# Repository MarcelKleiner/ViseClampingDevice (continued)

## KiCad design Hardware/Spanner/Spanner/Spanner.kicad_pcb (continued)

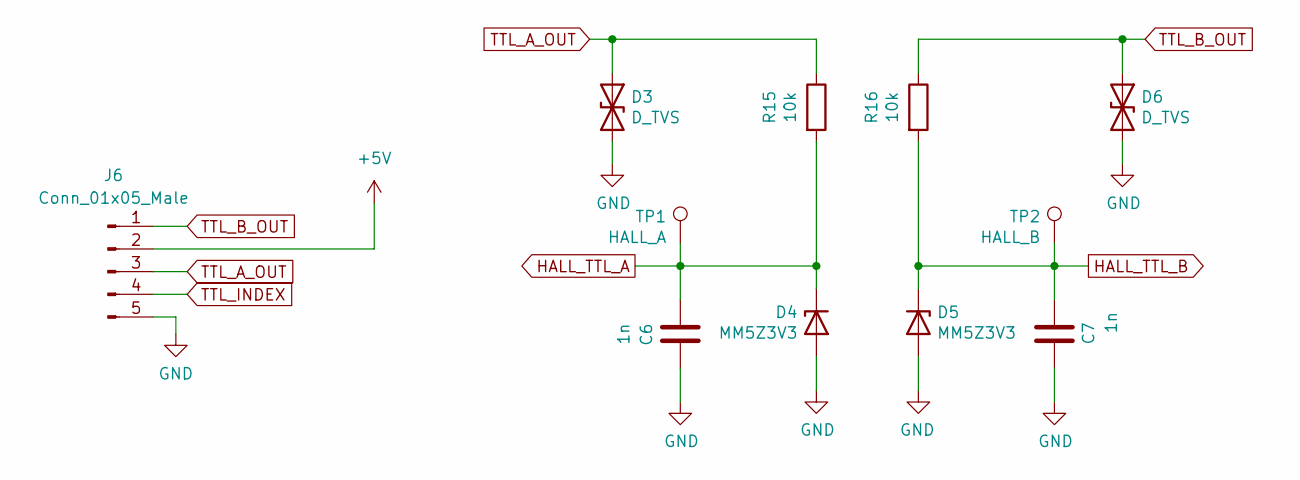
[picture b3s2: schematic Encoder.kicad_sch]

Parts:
C6, C7: 1n; C_0603_1608Metric; Mouser Nr. 581-06035C102K
D3, D6: D_TVS; D_0603_1608Metric; Mouser Nr. 652-CGA0603MLC-24E
D4, D5: MM5Z3V3; D_SOD-523; Mouser Nr. 863-MM5Z3V3T1G
J6: Conn_01x05_Male; PinHeader_1x05_P2.54mm_Vertical
R15, R16: 10k; R_0603_1608Metric; Mouser Nr. 603-RT0603FRE0710KL
TP1: HALL_A; TestPoint_Pad_D1.0mm
TP2: HALL_B; TestPoint_Pad_D1.0mm

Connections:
+5V: J6.2; also elsewhere on the board
GND: C6.1, C7.2, D3.2 (A2), D4.2 (A), D5.2 (A), D6.2 (A2), J6.5; also elsewhere on the board
HALL_TTL_A: C6.2, D4.1 (K), R15.2, TP1.1; also elsewhere on the board
HALL_TTL_B: C7.1, D5.1 (K), R16.2, TP2.1; also elsewhere on the board
TTL_A_OUT: D3.1 (A1), J6.3, R15.1
TTL_B_OUT: D6.1 (A1), J6.1, R16.1
TTL_INDEX: J6.4

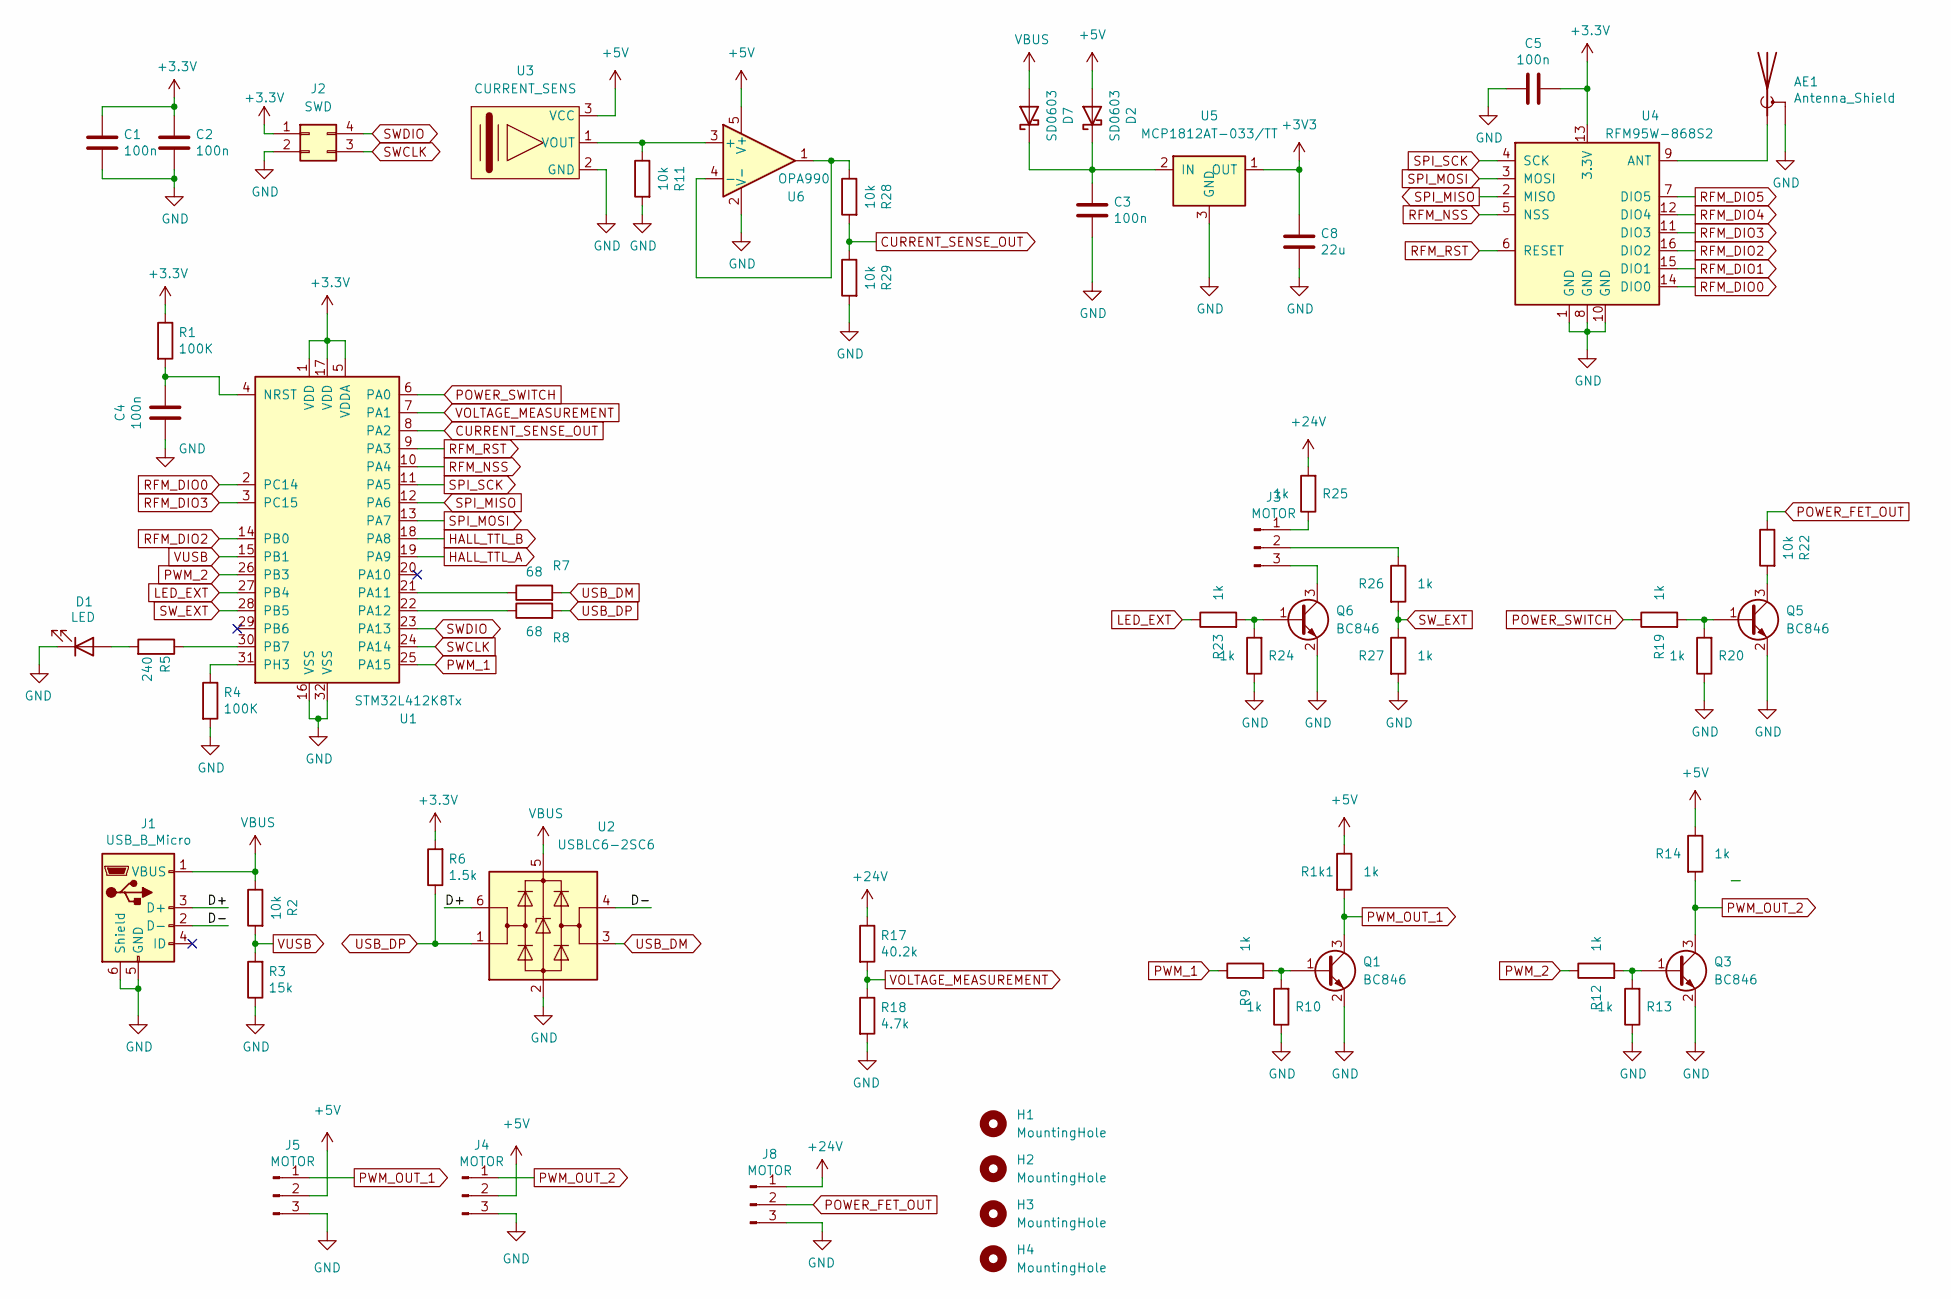
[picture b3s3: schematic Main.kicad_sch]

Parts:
AE1: Antenna_Shield; U.FL_Hirose_U.FL-R-SMT-1_Vertical; Mouser Nr. 712-CONUFL001-SMD-T
C1, C2, C3, C4, C5: 100n; C_0603_1608Metric; Mouser Nr. 187-CL10B104KB8NNWC
C8: 22u; C_0603_1608Metric; Mouser Nr. 187-CL21A226MAYNNNE
D1: LED; LED_0603_1608Metric; Mouser Nr. 710-150060VS75000
D2, D7: SD0603; D_0603_1608Metric; Mouser Nr. 581-SD0603S040S0R2
H1, H2, H3, H4: MountingHole; MountingHole_3.2mm_M3
J1: USB_B_Micro; USB_Micro-B_Wuerth_614105150721_Vertical; Mouser Nr. 710-614105150721
J2: SWD; PinHeader_2x02_P2.54mm_Vertical
J3, J4, J5, J8: MOTOR; PinHeader_1x03_P2.54mm_Vertical
Q1, Q3, Q5, Q6: BC846; SOT-23; Mouser Nr. 771-BC846A235
R1, R4: 100K; R_0603_1608Metric; Mouser Nr. 71-CRCW0603100KFKEAC
R1k1, R9, R10, R12, R13, R14, R19, R20, R23, R24, R25, R26, R27: 1k; R_0603_1608Metric; Mouser Nr. 603-RT0603FRE071KL
R2, R11, R22, R28, R29: 10k; R_0603_1608Metric; Mouser Nr. 603-RT0603FRE0710KL
R3: 15k; R_0603_1608Metric; Mouser Nr. 603-RT0603BRB0715KL
R5: 240; R_0603_1608Metric; Mouser Nr. 603-RC0603FR-13240RL
R6: 1.5k; R_0603_1608Metric; Mouser Nr. 603-RT0603FRE101K5L
R7, R8: 68; R_0603_1608Metric; Mouser Nr. 71-CRCW0603-68-E3
R17: 40.2k; R_0603_1608Metric; Mouser Nr. 754-RR0816P-4022D59C
R18: 4.7k; R_0603_1608Metric; Mouser Nr. 603-RT0603FRE074K7L
U1: STM32L412K8Tx; LQFP-32_7x7mm_P0.8mm; Mouser Nr. 511-STM32L412K8T6
U2: USBLC6-2SC6; SOT-23-6; Mouser Nr. 511-USBLC6-2SC6
U3: CURRENT_SENS; L01Z; Mouser Nr. 838-L01Z050S05
U4: RFM95W-868S2; HOPERF_RFM9XW_SMD; Mouser Nr. 223-RFM95W-868S2
U5: MCP1812AT-033/TT; SOT-23; Mouser Nr. 579-MCP1812AT-033/TT
U6: OPA990; SOT-23-5; Mouser Nr. 595-OPA990IDBVR

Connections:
+5V: D2.2 (A), J4.2, J5.2, R1k1.1, R14.1, U3.3 (VCC), U6.5 (V+); also elsewhere on the board
+24V: J8.1, R17.1, R25.2
/Main/D+: J1.3 (D+), U2.6 (I/O1)
/Main/D-: J1.2 (D-), U2.4 (I/O2)
CURRENT_SENSE_OUT: R28.2, R29.1, U1.8 (PA2)
GND: AE1.2 (Shield), C1.2, C2.2, C3.2, C4.1, C5.1, C8.1, D1.1 (K), J1.5 (GND), J1.6 (Shield), J2.2, J4.3, J5.3, J8.3, Q1.2 (E), Q3.2 (E), Q5.2 (E), Q6.2 (E), R3.1, R4.2, R10.1, R11.2, R13.1, R18.2, R20.1, R24.1, R27.2, R29.2, U1.16 (VSS), U1.32 (VSS), U2.2 (GND), U3.2 (GND), U4.1 (GND), U4.8 (GND), U4.10 (GND), U5.3 (GND), U6.2 (V-); also elsewhere on the board
HALL_TTL_A: U1.19 (PA9); also elsewhere on the board
HALL_TTL_B: U1.18 (PA8); also elsewhere on the board
LED_EXT: R23.1, U1.27 (PB4)
unnamed: AE1.1 (A), U4.9 (ANT)
unnamed: C3.1, D2.1 (K), D7.1 (K), U5.2 (IN)
unnamed: C4.2, R1.2, U1.4 (NRST)
unnamed: D1.2 (A), R5.2
unnamed: J3.1, R25.1
unnamed: J3.2, R26.1
unnamed: J3.3, Q6.3 (C)
unnamed: Q1.1 (B), R9.2, R10.2
unnamed: Q3.1 (B), R12.2, R13.2
unnamed: Q5.1 (B), R19.2, R20.2
unnamed: Q5.3 (C), R22.2
unnamed: Q6.1 (B), R23.2, R24.2
unnamed: R4.1, U1.31 (PH3)
unnamed: R5.1, U1.30 (PB7)
unnamed: R7.1, U1.21 (PA11)
unnamed: R8.1, U1.22 (PA12)
unnamed: R11.1, U3.1 (VOUT), U6.3 (+)
unnamed: R28.1, U6.1, U6.4 (-)
POWER_FET_OUT: J8.2, R22.1
POWER_SWITCH: R19.1, U1.6 (PA0)
PWM_1: R9.1, U1.25 (PA15)
PWM_2: R12.1, U1.26 (PB3)
PWM_OUT_1: J5.1, Q1.3 (C), R1k1.2
PWM_OUT_2: J4.1, Q3.3 (C), R14.2
RFM_DIO0: U1.2 (PC14), U4.14 (DIO0)
RFM_DIO1: U4.15 (DIO1)
RFM_DIO2: U1.14 (PB0), U4.16 (DIO2)
RFM_DIO3: U1.3 (PC15), U4.11 (DIO3)
RFM_DIO4: U4.12 (DIO4)
RFM_DIO5: U4.7 (DIO5)
RFM_NSS: U1.10 (PA4), U4.5 (NSS)
RFM_RST: U1.9 (PA3), U4.6 (RESET)
SPI_MISO: U1.12 (PA6), U4.2 (MISO)
SPI_MOSI: U1.13 (PA7), U4.3 (MOSI)
SPI_SCK: U1.11 (PA5), U4.4 (SCK)
SWCLK: J2.3, U1.24 (PA14)
SWDIO: J2.4, U1.23 (PA13)
SW_EXT: R26.2, R27.1, U1.28 (PB5)
USB_DM: R7.2, U2.3 (I/O2)
USB_DP: R6.1, R8.2, U2.1 (I/O1)
VBUS: D7.2 (A), J1.1 (VBUS), R2.1, U2.5 (VBUS)
VOLTAGE_MEASUREMENT: R17.2, R18.1, U1.7 (PA1)
VUSB: R2.2, R3.2, U1.15 (PB1)

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
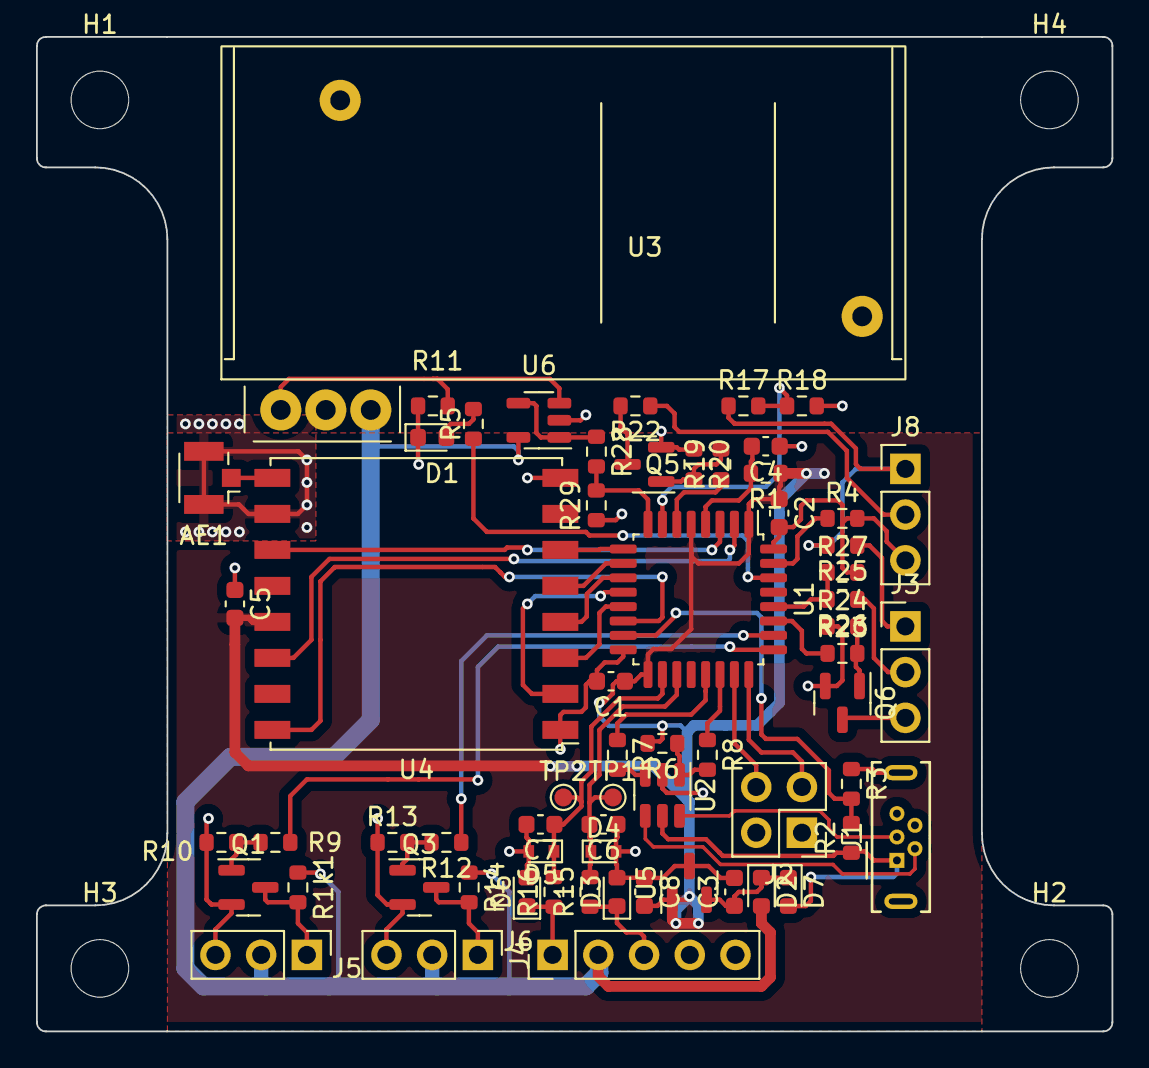
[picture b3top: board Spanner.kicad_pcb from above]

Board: 2 copper layers, 59.8 x 55.2 mm, 68 parts (0 on the bottom side), 52 nets.

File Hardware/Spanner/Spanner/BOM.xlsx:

Item | Qty | Reference(s) | Value | Hersteller Nr. | Mouser Nr.
1 | 1 | AE1 | Antenna_Shield | CONUFL001-SMD-T | 712-CONUFL001-SMD-T
2 | 5 | C1, C2, C3, C4, C5 | 100n | CL10B104KB8NNWC | 187-CL10B104KB8NNWC
3 | 2 | C6, C7 | 1n | 06035C102KAT2A | 581-06035C102K
4 | 1 | C8 | 22u | CL21A226MAYNNNE | 187-CL21A226MAYNNNE
5 | 1 | D1 | LED | 150060VS75000 | 710-150060VS75000
6 | 1 | D2 | SD0603 | SD0603S040S0R2 | 581-SD0603S040S0R2
7 | 2 | D3, D6 | D_TVS | CGA0603MLC-24E | 652-CGA0603MLC-24E
8 | 2 | D4, D5 | MM5Z3V3 | MM5Z3V3T1G | 863-MM5Z3V3T1G
10 | 1 | J1 | USB_B_Micro | 614105150721 | 710-614105150721
15 | 4 | Q1, Q3, Q5, Q6 | BC846 | BC846A,235 | 771-BC846A235
16 | 2 | R1, R4 | 100K | CRCW0603100KFKEAC | 71-CRCW0603100KFKEAC
17 | 13 | R1k1, R9, R10, R12, R13, R14, R19, R20, R23, R24, R25, R26, R27 | 1k | RT0603FRE071KL | 603-RT0603FRE071KL
18 | 8 | R2, R11, R15, R16, R21, R22, R28, R29 | 10k | RT0603FRE0710KL | 603-RT0603FRE0710KL
19 | 1 | R3 | 15k | RT0603BRB0715KL | 603-RT0603BRB0715KL
20 | 1 | R5 | 240 | RC0603FR-13240RL | 603-RC0603FR-13240RL
21 | 1 | R6 | 1.5k | RT0603FRE101K5L | 603-RT0603FRE101K5L
22 | 2 | R7, R8 | 68 | CRCW060368R0FKEA | 71-CRCW0603-68-E3
23 | 1 | R17 | 40.2k | RR0816P-4022-D-59C | 754-RR0816P-4022D59C
24 | 1 | R18 | 4.7k | RT0603FRE074K7 | 603-RT0603FRE074K7L
27 | 1 | U1 | STM32L412K8Tx | STM32L412K8T6 | 511-STM32L412K8T6
28 | 1 | U2 | USBLC6-2SC6 | USBLC6-2SC6 | 511-USBLC6-2SC6
29 | 1 | U3 | CURRENT_SENS | L01Z050S05 | 838-L01Z050S05
30 | 1 | U4 | RFM95W-868S2 | RFM95W-868S2 | 223-RFM95W-868S2
31 | 1 | U5 | MCP1812AT-033/TT | MCP1812AT-033/TT | 579-MCP1812AT-033/TT
32 | 1 | U6 | OPA990 | OPA990IDBVR | 595-OPA990IDBVR

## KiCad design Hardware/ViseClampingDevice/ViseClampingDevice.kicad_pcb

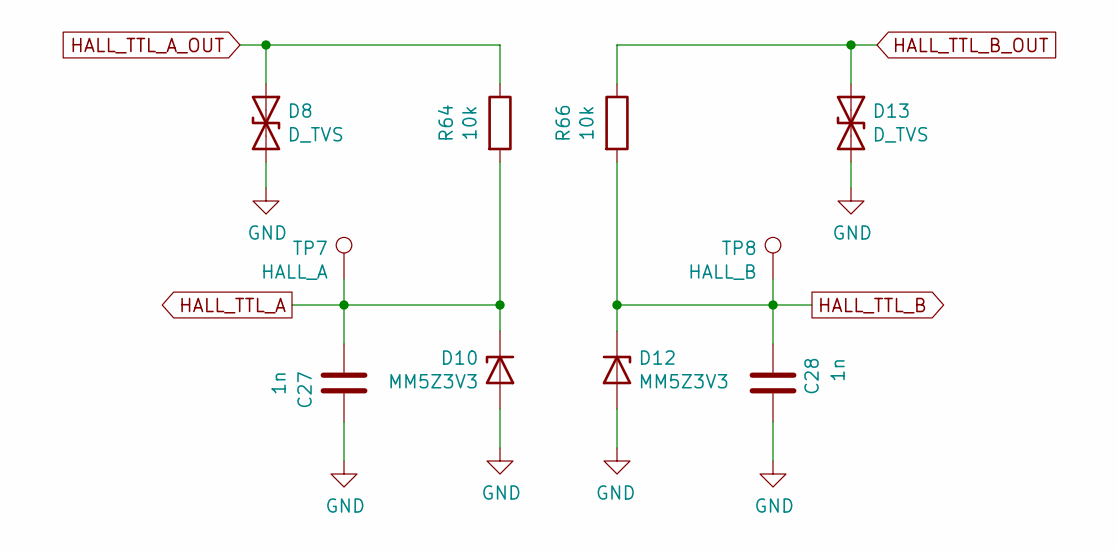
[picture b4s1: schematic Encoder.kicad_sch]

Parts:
C27, C28: 1n; C_0603_1608Metric; Mouser Nr. 581-06035C102K
D8, D13: D_TVS; D_0603_1608Metric; Mouser Nr. 833-MLESD24B-0603-TP
D10, D12: MM5Z3V3; D_SOD-523; Mouser Nr. 863-MM5Z3V3T1G
R64, R66: 10k; R_0603_1608Metric; Mouser Nr. 603-RT0603FRE0710KL
TP7: HALL_A; TestPoint_Pad_D1.0mm
TP8: HALL_B; TestPoint_Pad_D1.0mm

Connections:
GND: C27.1, C28.2, D8.2 (A2), D10.2 (A), D12.2 (A), D13.2 (A2); also elsewhere on the board
HALL_TTL_A: C27.2, D10.1 (K), R64.2, TP7.1
HALL_TTL_A_OUT: D8.1 (A1), R64.1; also elsewhere on the board
HALL_TTL_B: C28.1, D12.1 (K), R66.2, TP8.1
HALL_TTL_B_OUT: D13.1 (A1), R66.1; also elsewhere on the board

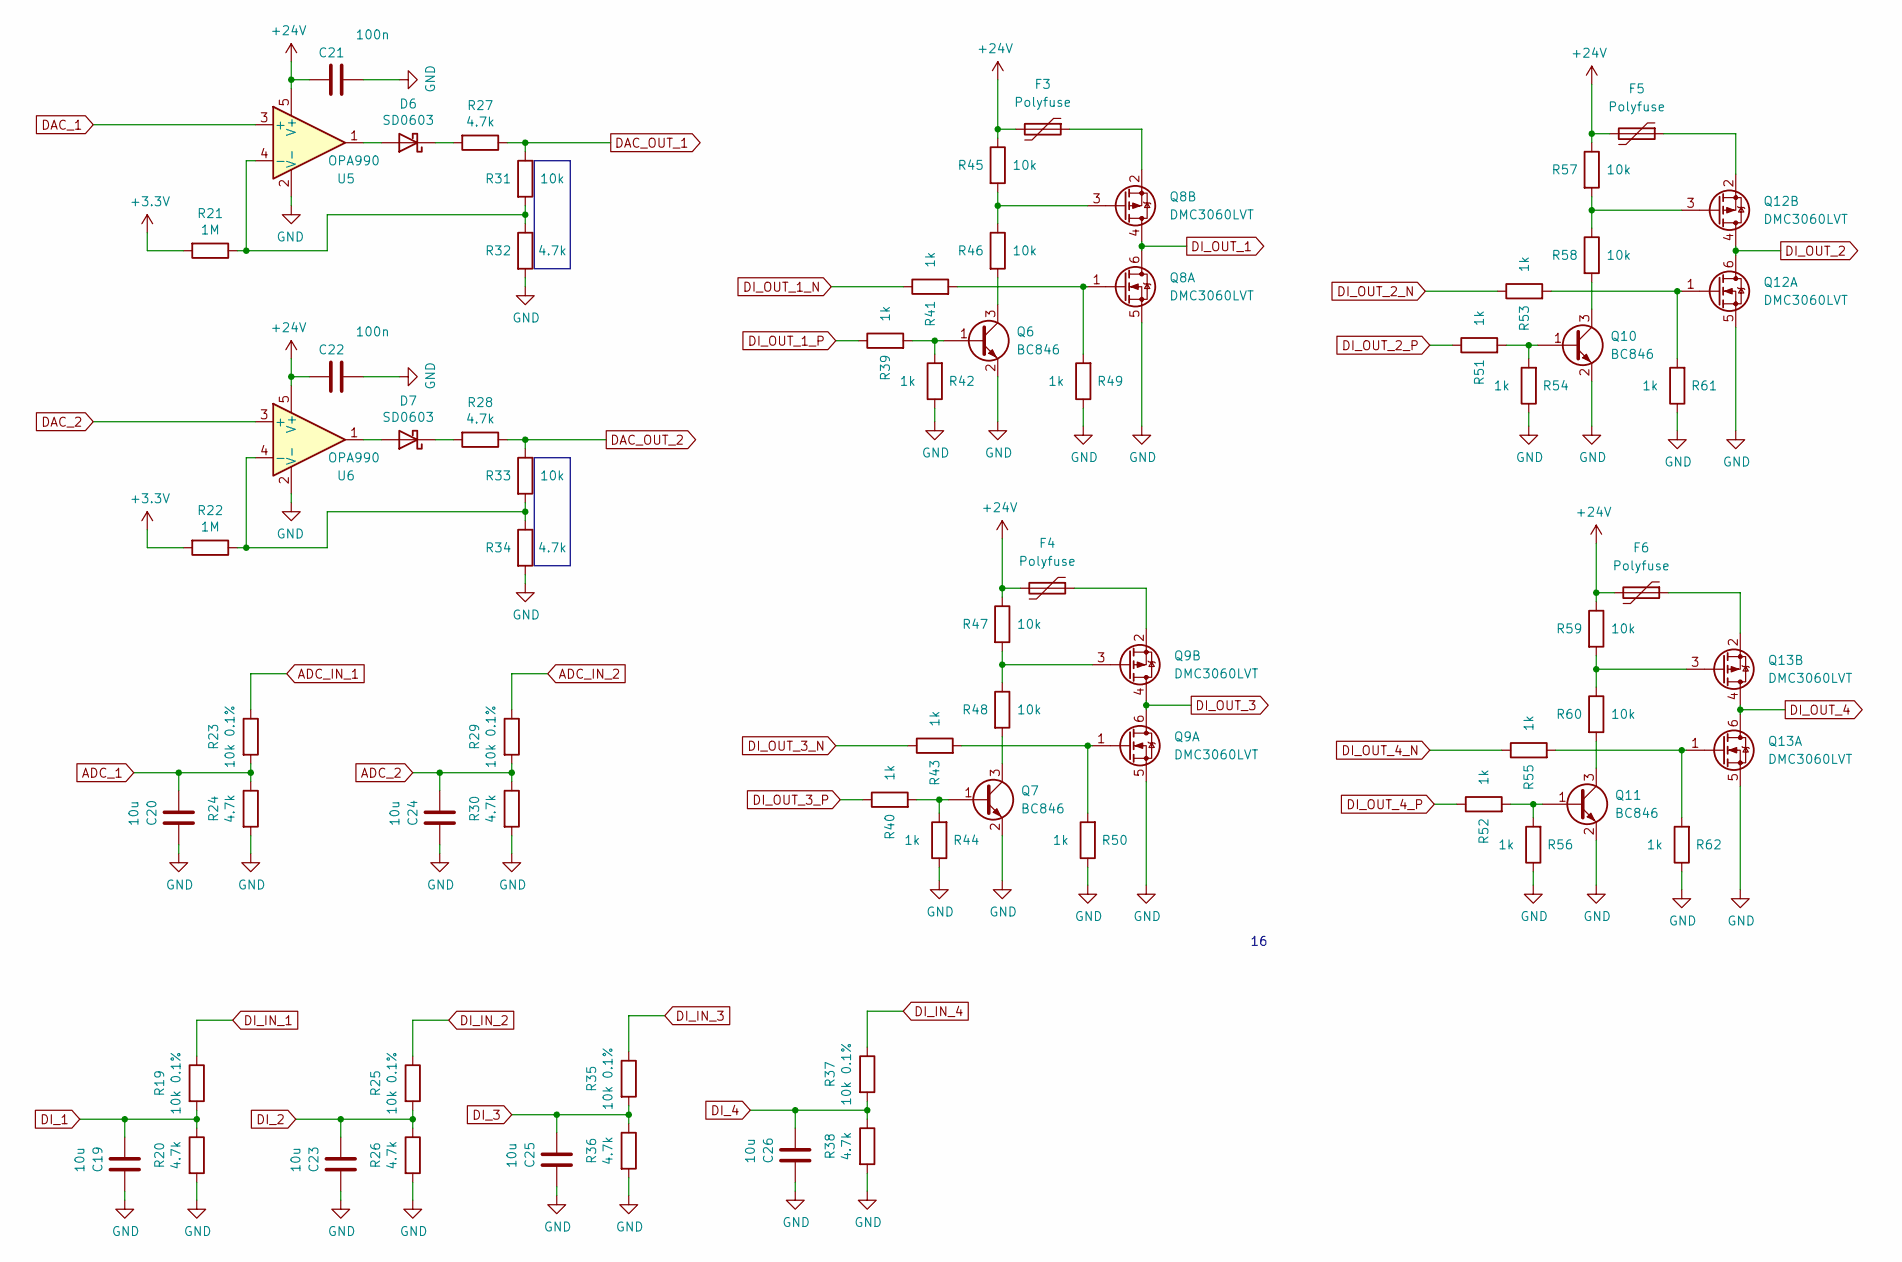
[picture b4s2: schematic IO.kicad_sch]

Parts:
C19, C20, C23, C24, C25, C26: 10u; C_0603_1608Metric; Mouser Nr. 187-CL10X106MO8NRNC
C21, C22: 100n; C_0603_1608Metric; Mouser Nr. 187-CL10B104KB8NNWC
D6, D7: SD0603; D_0603_1608Metric; Mouser Nr. 581-SD0603S040S0R2
F3, F4, F5, F6: Polyfuse; Fuse_0603_1608Metric
Q6, Q7, Q10, Q11: BC846; SOT-23
Q8, Q9, Q12, Q13: DMC3060LVT; TSOT-23-6
R19, R23, R25, R29, R35, R37: 10k 0.1%; R_0603_1608Metric; Mouser Nr. 284-APC0603B10K0N
R20, R24, R26, R27, R28, R30, R32, R34, R36, R38: 4.7k; R_0603_1608Metric; Mouser Nr. 754-RR0816P-472D
R21, R22: 1M; R_0603_1608Metric; Mouser Nr. 667-ERJ-3GEYJ105V
R31, R33, R45, R46, R47, R48, R57, R58, R59, R60: 10k; R_0603_1608Metric; Mouser Nr. 603-RT0603FRE0710KL
R39, R40, R41, R42, R43, R44, R49, R50, R51, R52, R53, R54, R55, R56, R61, R62: 1k; R_0603_1608Metric
U5, U6: OPA990; SOT-23-5; Mouser Nr. 595-OPA990IDBVR

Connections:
+24V: C21.1, C22.1, F3.2, F4.2, F5.2, F6.2, R45.1, R47.1, R57.1, R59.1, U5.5 (V+), U6.5 (V+); also elsewhere on the board
ADC_1: C20.1, R23.2, R24.1
ADC_2: C24.1, R29.2, R30.1
ADC_IN_1: R23.1; also elsewhere on the board
ADC_IN_2: R29.1; also elsewhere on the board
DAC_1: U5.3 (+); also elsewhere on the board
DAC_2: U6.3 (+); also elsewhere on the board
DAC_OUT_1: R27.1, R31.1; also elsewhere on the board
DAC_OUT_2: R28.1, R33.1; also elsewhere on the board
DI_1: C19.1, R19.2, R20.1; also elsewhere on the board
DI_2: C23.1, R25.2, R26.1; also elsewhere on the board
DI_3: C25.1, R35.2, R36.1; also elsewhere on the board
DI_4: C26.1, R37.2, R38.1; also elsewhere on the board
DI_IN_1: R19.1; also elsewhere on the board
DI_IN_2: R25.1; also elsewhere on the board
DI_IN_3: R35.1; also elsewhere on the board
DI_IN_4: R37.1; also elsewhere on the board
DI_OUT_1: Q8.4 (D), Q8.6 (D); also elsewhere on the board
DI_OUT_1_N: R41.1; also elsewhere on the board
DI_OUT_1_P: R39.1; also elsewhere on the board
DI_OUT_2: Q12.4 (D), Q12.6 (D); also elsewhere on the board
DI_OUT_2_N: R53.1; also elsewhere on the board
DI_OUT_2_P: R51.1; also elsewhere on the board
DI_OUT_3: Q9.4 (D), Q9.6 (D); also elsewhere on the board
DI_OUT_3_N: R43.1; also elsewhere on the board
DI_OUT_3_P: R40.1; also elsewhere on the board
DI_OUT_4: Q13.4 (D), Q13.6 (D); also elsewhere on the board
DI_OUT_4_N: R55.1; also elsewhere on the board
DI_OUT_4_P: R52.1; also elsewhere on the board
GND: C19.2, C20.2, C21.2, C22.2, C23.2, C24.2, C25.2, C26.2, Q6.2 (E), Q7.2 (E), Q8.5 (S), Q9.5 (S), Q10.2 (E), Q11.2 (E), Q12.5 (S), Q13.5 (S), R20.2, R24.2, R26.2, R30.2, R32.2, R34.2, R36.2, R38.2, R42.1, R44.1, R49.1, R50.1, R54.1, R56.1, R61.1, R62.1, U5.2 (V-), U6.2 (V-); also elsewhere on the board
unnamed: D6.1 (K), R27.2
unnamed: D6.2 (A), U5.1
unnamed: D7.1 (K), R28.2
unnamed: D7.2 (A), U6.1
unnamed: F3.1, Q8.2 (S)
unnamed: F4.1, Q9.2 (S)
unnamed: F5.1, Q12.2 (S)
unnamed: F6.1, Q13.2 (S)
unnamed: Q6.1 (B), R39.2, R42.2
unnamed: Q6.3 (C), R46.2
unnamed: Q7.1 (B), R40.2, R44.2
unnamed: Q7.3 (C), R48.2
unnamed: Q8.1 (G), R41.2, R49.2
unnamed: Q8.3 (G), R45.2, R46.1
unnamed: Q9.1 (G), R43.2, R50.2
unnamed: Q9.3 (G), R47.2, R48.1
unnamed: Q10.1 (B), R51.2, R54.2
unnamed: Q10.3 (C), R58.2
unnamed: Q11.1 (B), R52.2, R56.2
unnamed: Q11.3 (C), R60.2
unnamed: Q12.1 (G), R53.2, R61.2
unnamed: Q12.3 (G), R57.2, R58.1
unnamed: Q13.1 (G), R55.2, R62.2
unnamed: Q13.3 (G), R59.2, R60.1
unnamed: R21.1, R31.2, R32.1, U5.4 (-)
unnamed: R22.1, R33.2, R34.1, U6.4 (-)

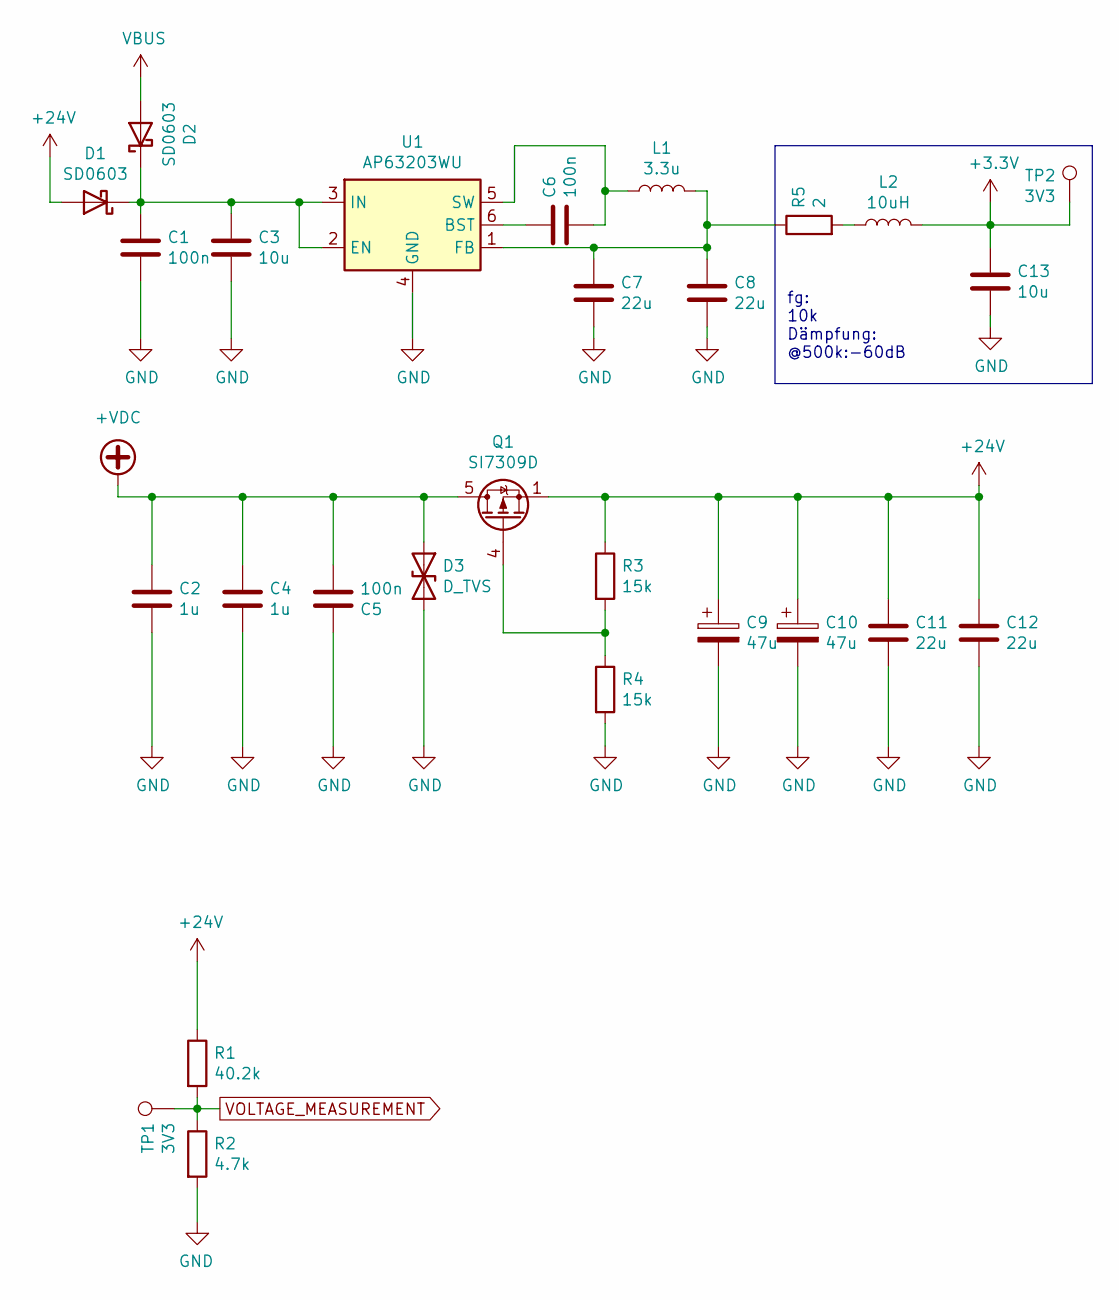
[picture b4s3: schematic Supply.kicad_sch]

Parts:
C1, C5, C6: 100n; C_0603_1608Metric; Mouser Nr. 187-CL10B104KB8NNWC
C2: 1u; C_0603_1608Metric
C3: 10u; C_0603_1608Metric
C4: 1u; C_0603_1608Metric; Mouser Nr. 187-CL10X106MO8NRNC
C7, C8: 22u; C_0603_1608Metric
C9, C10: 47u; CP_Elec_5x5.8; Mouser Nr. 667-EEE-FT1V470AR
C11, C12: 22u; C_0805_2012Metric
C13: 10u; C_0603_1608Metric; Mouser Nr. 187-CL10X106MO8NRNC
D1, D2: SD0603; D_0603_1608Metric; Mouser Nr. 581-SD0603S040S0R2
D3: D_TVS; D_0603_1608Metric; Mouser Nr. 833-MLESD24B-0603-TP
L1: 3.3u; L_0805_2012Metric
L2: 10uH; L_0603_1608Metric; Mouser Nr. 81-LQM18DH100M70L
Q1: SI7309D; Vishay_PowerPAK_1212-8_Single; Mouser Nr. 781-SI7309DN-T1-E3
R1: 40.2k; R_0603_1608Metric; Mouser Nr. 754-RR0816P-4022D59C
R2: 4.7k; R_0603_1608Metric; Mouser Nr. 754-RR0816P-472D
R3, R4: 15k; R_0603_1608Metric; Mouser Nr. 667-ERJ-3EKF1502V
R5: 2; R_0603_1608Metric; Mouser Nr. 652-CR0603-J/-2R0ELF
TP1, TP2: 3V3; TestPoint_Pad_D1.0mm
U1: AP63203WU; TSOT-23-6

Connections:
+24V: C9.1, C10.1, C11.2, C12.2, D1.2 (A), Q1.1 (S), Q1.2 (S), Q1.3 (S), R1.1, R3.1; also elsewhere on the board
+VDC: C2.2, C4.2, C5.1, D3.1 (A1), Q1.5 (D); also elsewhere on the board
GND: C1.2, C2.1, C3.2, C4.1, C5.2, C7.1, C8.1, C9.2, C10.2, C11.1, C12.1, C13.1, D3.2 (A2), R2.2, R4.2, U1.4 (GND); also elsewhere on the board
unnamed: C1.1, C3.1, D1.1 (K), D2.1 (K), U1.2 (EN), U1.3 (IN)
unnamed: C6.1, L1.1, U1.5 (SW)
unnamed: C6.2, U1.6 (BST)
unnamed: C7.2, C8.2, L1.2, R5.1, U1.1 (FB)
unnamed: L2.1, R5.2
unnamed: Q1.4 (G), R3.2, R4.1
VBUS: D2.2 (A); also elsewhere on the board
VOLTAGE_MEASUREMENT: R1.2, R2.1, TP1.1

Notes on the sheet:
fg: 10k Dämpfung: @500k:-60dB

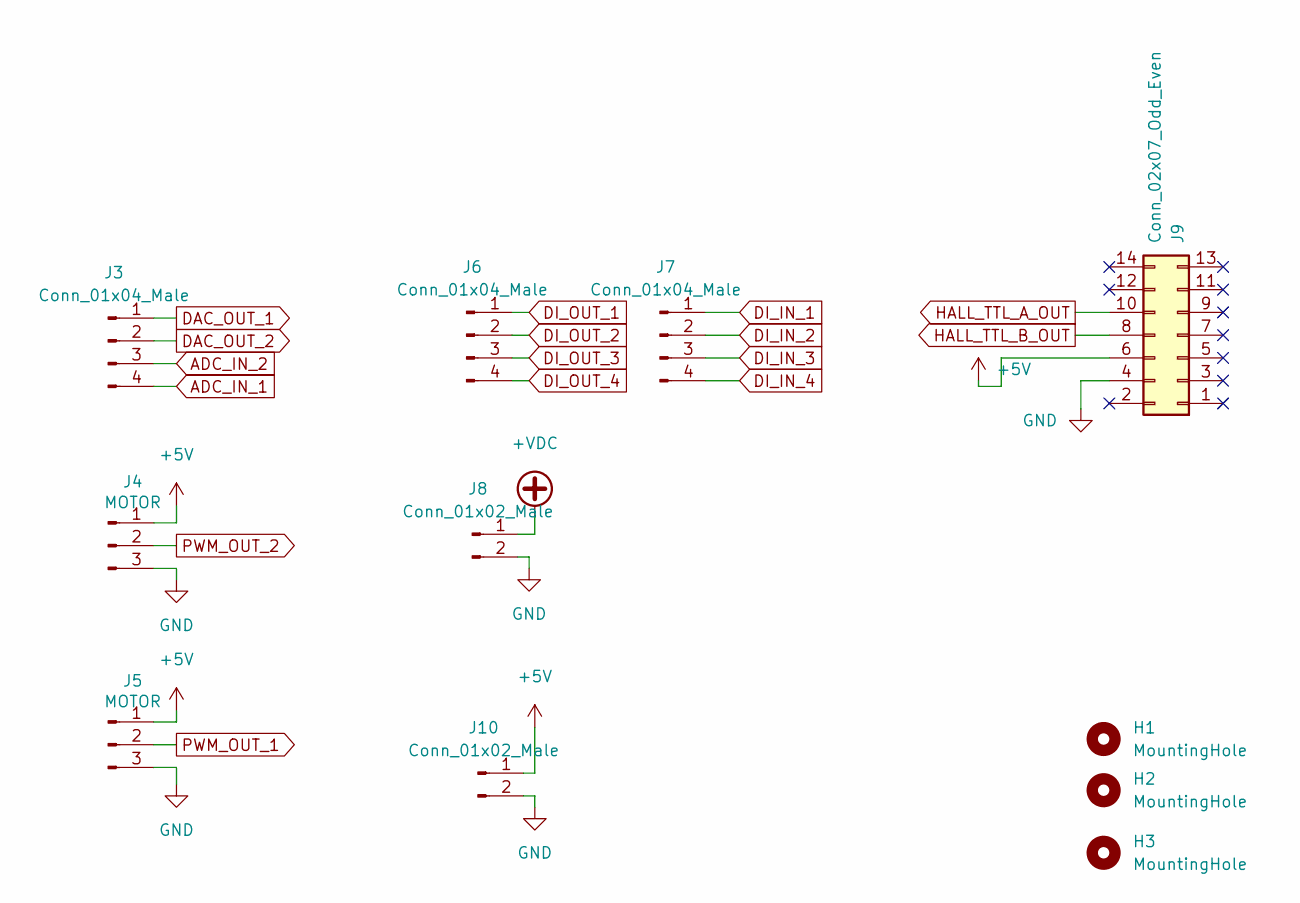
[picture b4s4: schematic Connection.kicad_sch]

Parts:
H1, H2, H3: MountingHole; MountingHole_3.2mm_M3
J3, J6, J7: Conn_01x04_Male; PinHeader_1x04_P2.54mm_Vertical
J4, J5: MOTOR; PinHeader_1x03_P2.54mm_Vertical; Mouser Nr. 200-TSW-103-15-T-S
J8, J10: Conn_01x02_Male; PinHeader_1x02_P2.54mm_Vertical
J9: Conn_02x07_Odd_Even; PinHeader_2x07_P1.27mm_Vertical_SMD

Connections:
+5V: J4.1, J5.1, J9.6, J10.1; also elsewhere on the board
+VDC: J8.1; also elsewhere on the board
ADC_IN_1: J3.4; also elsewhere on the board
ADC_IN_2: J3.3; also elsewhere on the board
DAC_OUT_1: J3.1; also elsewhere on the board
DAC_OUT_2: J3.2; also elsewhere on the board
DI_IN_1: J7.1; also elsewhere on the board
DI_IN_2: J7.2; also elsewhere on the board
DI_IN_3: J7.3; also elsewhere on the board
DI_IN_4: J7.4; also elsewhere on the board
DI_OUT_1: J6.1; also elsewhere on the board
DI_OUT_2: J6.2; also elsewhere on the board
DI_OUT_3: J6.3; also elsewhere on the board
DI_OUT_4: J6.4; also elsewhere on the board
GND: J4.3, J5.3, J8.2, J9.4, J10.2; also elsewhere on the board
HALL_TTL_A_OUT: J9.10; also elsewhere on the board
HALL_TTL_B_OUT: J9.8; also elsewhere on the board
PWM_OUT_1: J5.2; also elsewhere on the board
PWM_OUT_2: J4.2; also elsewhere on the board

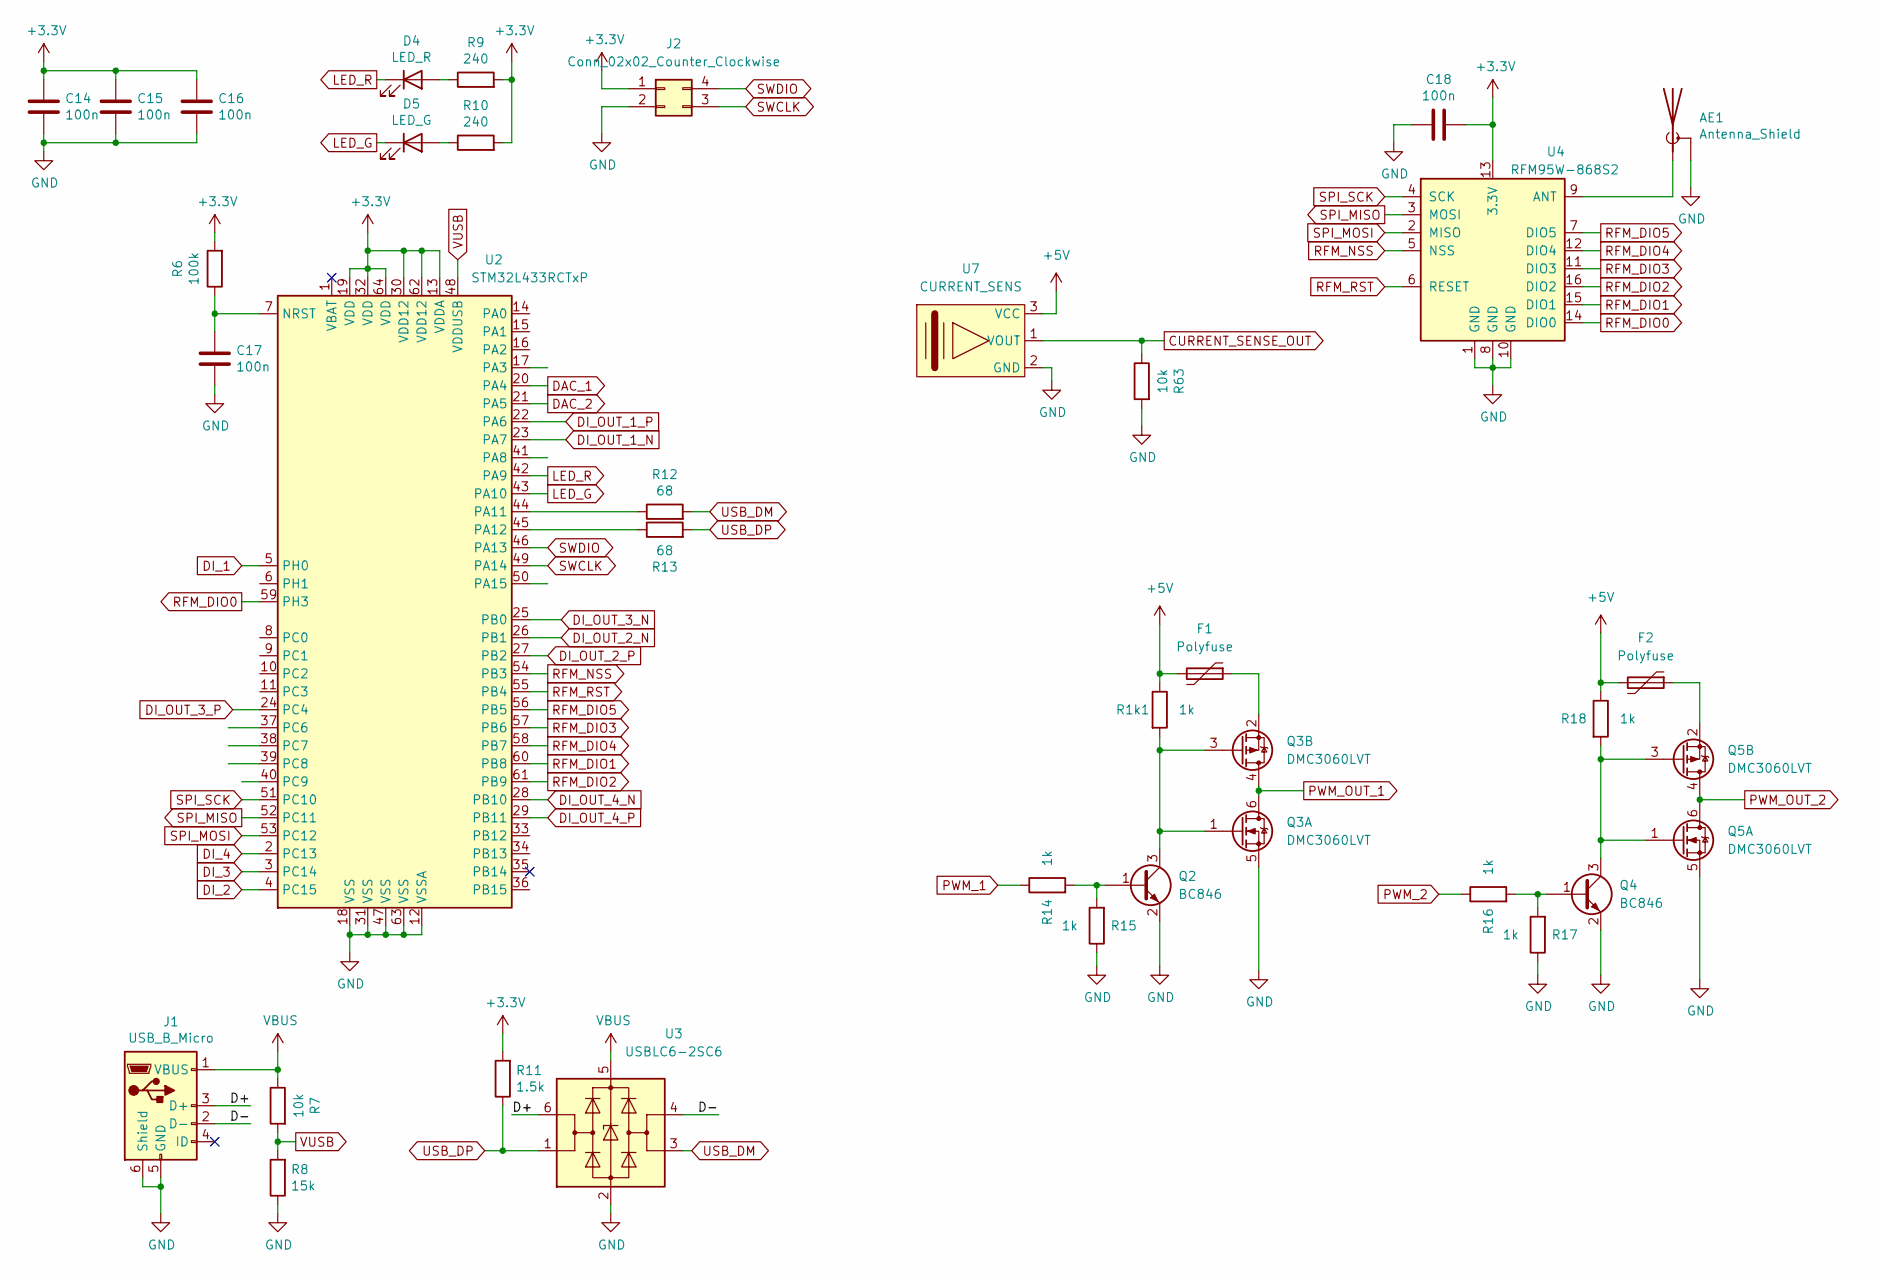
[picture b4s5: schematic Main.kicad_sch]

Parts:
AE1: Antenna_Shield; U.FL_Hirose_U.FL-R-SMT-1_Vertical; MPN CONUFL001-SMD-T
C14, C15, C16, C17: 100n; C_0603_1608Metric; Mouser Nr. 187-CL10B104KB8NNWC
C18: 100n; C_0603_1608Metric
D4: LED_R; LED_0603_1608Metric; Mouser Nr. 696-SMLLXFP0603SICTR
D5: LED_G; LED_0603_1608Metric; Mouser Nr. 696-SMLLXFP0603SUGCT
F1, F2: Polyfuse; Fuse_0603_1608Metric
J1: USB_B_Micro; USB_Micro-B_Wuerth_614105150721_Vertical; Mouser Nr. 710-614105150721
J2: Conn_02x02_Counter_Clockwise; PinHeader_2x02_P2.54mm_Vertical
Q2, Q4: BC846; SOT-23
Q3, Q5: DMC3060LVT; TSOT-23-6
R1k1, R14, R15, R16, R17, R18: 1k; R_0603_1608Metric
R6: 100k; R_0603_1608Metric; Mouser Nr. 71-CRCW0603100KFKEAC
R7, R63: 10k; R_0603_1608Metric; Mouser Nr. 603-RT0603FRE0710KL
R8: 15k; R_0603_1608Metric; Mouser Nr. 667-ERJ-3EKF1502V
R9, R10: 240; R_0603_1608Metric; Mouser Nr. 603-RC0603FR-13240RL
R11: 1.5k; R_0603_1608Metric
R12, R13: 68; R_0603_1608Metric; Mouser Nr. 71-CRCW0603-68-E3
U2: STM32L433RCTxP; LQFP-64_10x10mm_P0.5mm
U3: USBLC6-2SC6; SOT-23-6; Mouser Nr. 511-USBLC6-2SC6
U4: RFM95W-868S2; HOPERF_RFM9XW_SMD
U7: CURRENT_SENS; L01Z

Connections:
+5V: F1.2, F2.2, R1k1.1, R18.1, U7.3 (VCC); also elsewhere on the board
/Main/D+: J1.3 (D+), U3.6 (I/O1)
/Main/D-: J1.2 (D-), U3.4 (I/O2)
CURRENT_SENSE_OUT: R63.1, U7.1 (VOUT)
DAC_1: U2.20 (PA4); also elsewhere on the board
DAC_2: U2.21 (PA5); also elsewhere on the board
DI_1: U2.5 (PH0); also elsewhere on the board
DI_2: U2.4 (PC15); also elsewhere on the board
DI_3: U2.3 (PC14); also elsewhere on the board
DI_4: U2.2 (PC13); also elsewhere on the board
DI_OUT_1_N: U2.23 (PA7); also elsewhere on the board
DI_OUT_1_P: U2.22 (PA6); also elsewhere on the board
DI_OUT_2_N: U2.26 (PB1); also elsewhere on the board
DI_OUT_2_P: U2.27 (PB2); also elsewhere on the board
DI_OUT_3_N: U2.25 (PB0); also elsewhere on the board
DI_OUT_3_P: U2.24 (PC4); also elsewhere on the board
DI_OUT_4_N: U2.28 (PB10); also elsewhere on the board
DI_OUT_4_P: U2.29 (PB11); also elsewhere on the board
GND: AE1.2 (Shield), C14.2, C15.2, C16.2, C17.2, C18.1, J1.5 (GND), J1.6 (Shield), J2.2, Q2.2 (E), Q3.5 (S), Q4.2 (E), Q5.5 (S), R8.1, R15.1, R17.1, R63.2, U2.12 (VSSA), U2.18 (VSS), U2.31 (VSS), U2.47 (VSS), U2.63 (VSS), U3.2 (GND), U4.1 (GND), U4.8 (GND), U4.10 (GND), U7.2 (GND); also elsewhere on the board
LED_G: D5.1 (K), U2.43 (PA10)
LED_R: D4.1 (K), U2.42 (PA9)
unnamed: AE1.1 (A), U4.9 (ANT)
unnamed: C17.1, R6.1, U2.7 (NRST)
unnamed: D4.2 (A), R9.1
unnamed: D5.2 (A), R10.1
unnamed: F1.1, Q3.2 (S)
unnamed: F2.1, Q5.2 (S)
unnamed: Q2.1 (B), R14.2, R15.2
unnamed: Q2.3 (C), Q3.1 (G), Q3.3 (G), R1k1.2
unnamed: Q4.1 (B), R16.2, R17.2
unnamed: Q4.3 (C), Q5.1 (G), Q5.3 (G), R18.2
unnamed: R12.1, U2.44 (PA11)
unnamed: R13.1, U2.45 (PA12)
PWM_1: R14.1
PWM_2: R16.1
PWM_OUT_1: Q3.4 (D), Q3.6 (D); also elsewhere on the board
PWM_OUT_2: Q5.4 (D), Q5.6 (D); also elsewhere on the board
RFM_DIO0: U2.59 (PH3), U4.14 (DIO0)
RFM_DIO1: U2.60 (PB8), U4.15 (DIO1)
RFM_DIO2: U2.61 (PB9), U4.16 (DIO2)
RFM_DIO3: U2.57 (PB6), U4.11 (DIO3)
RFM_DIO4: U2.58 (PB7), U4.12 (DIO4)
RFM_DIO5: U2.56 (PB5), U4.7 (DIO5)
RFM_NSS: U2.54 (PB3), U4.5 (NSS)
RFM_RST: U2.55 (PB4), U4.6 (RESET)
SPI_MISO: U2.52 (PC11), U4.3 (MOSI)
SPI_MOSI: U2.53 (PC12), U4.2 (MISO)
SPI_SCK: U2.51 (PC10), U4.4 (SCK)
SWCLK: J2.3, U2.49 (PA14)
SWDIO: J2.4, U2.46 (PA13)
USB_DM: R12.2, U3.3 (I/O2)
USB_DP: R11.1, R13.2, U3.1 (I/O1)
VBUS: J1.1 (VBUS), R7.1, U3.5 (VBUS); also elsewhere on the board
VUSB: R7.2, R8.2, U2.48 (VDDUSB)

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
